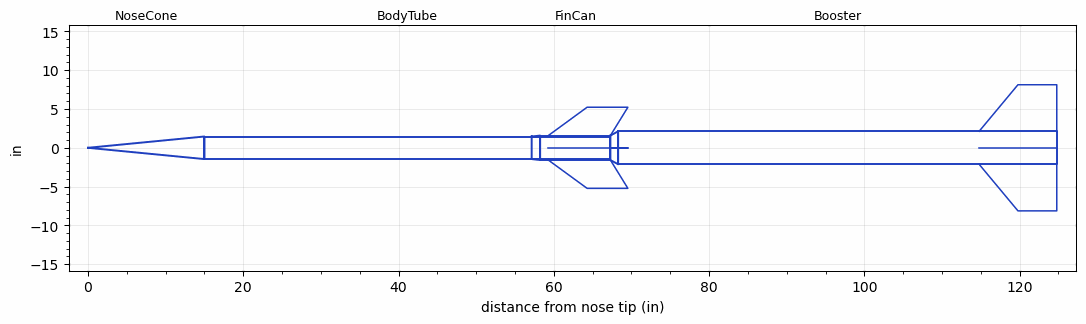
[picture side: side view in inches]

<RASAeroDocument>
 <FileVersion>2</FileVersion>
 <RocketDesign>
  <NoseCone>
   <Length>15</Length>
   <Diameter>2.91</Diameter>
   <Shape>Conical</Shape>
   <BluntRadius>0.1</BluntRadius>
   <Location>0</Location>
  </NoseCone>
  <BodyTube>
   <Length>52.29</Length>
   <Diameter>2.91</Diameter>
   <Location>15</Location>
  </BodyTube>
  <FinCan>
   <Length>9.05</Length>
   <Diameter>3.15</Diameter>
   <InsideDiameter>2.91</InsideDiameter>
   <Location>67.29</Location>
   <ShoulderLength>1.09</ShoulderLength>
   <Offset>-9.05</Offset>
   <Fin>
    <Count>4</Count>
    <Chord>8</Chord>
    <Span>3.65</Span>
    <SweepDistance>5</SweepDistance>
    <TipChord>5.25</TipChord>
    <Thickness>0.157</Thickness>
    <Location>8</Location>
    <AirfoilSection>Hexagonal</AirfoilSection>
    <FX1>1.015</FX1>
    <FX3>0.75</FX3>
   </Fin>
  </FinCan>
  <Booster>
   <Length>56.5</Length>
   <Diameter>4.25</Diameter>
   <InsideDiameter>3.15</InsideDiameter>
   <Location>67.29</Location>
   <ShoulderLength>1</ShoulderLength>
   <Fin>
    <Count>4</Count>
    <Chord>10</Chord>
    <Span>6</Span>
    <SweepDistance>5</SweepDistance>
    <TipChord>5</TipChord>
    <Thickness>0.187</Thickness>
    <Location>10</Location>
    <AirfoilSection>Hexagonal</AirfoilSection>
    <FX1>1</FX1>
    <FX3>0.75</FX3>
   </Fin>
  </Booster>
  <Surface>Rough Camouflage Paint</Surface>
  <ModifiedBarrowman>True</ModifiedBarrowman>
  <Turbulence>True</Turbulence>
  <UseBooster1>True</UseBooster1>
  <UseBooster2>False</UseBooster2>
 </RocketDesign>
 <LaunchSite>
  <Altitude>3701</Altitude>
  <Pressure>29.92</Pressure>
  <RodAngle>0</RodAngle>
  <RodLength>15</RodLength>
  <Temperature>45.8</Temperature>
  <WindSpeed>0</WindSpeed>
 </LaunchSite>
 <Recovery>
  <Altitude1>2000</Altitude1>
  <Altitude2>2000</Altitude2>
  <DeviceType1>Parachute</DeviceType1>
  <DeviceType2>Parachute</DeviceType2>
  <Event1>True</Event1>
  <Event2>True</Event2>
  <Size1>8</Size1>
  <Size2>28</Size2>
  <EventType1>Apogee</EventType1>
  <EventType2>Altitude</EventType2>
  <CD1>0.8</CD1>
  <CD2>1.8</CD2>
 </Recovery>
 <SimulationList>
  <Simulation>
   <SustainerEngine>N3364  (X)</SustainerEngine>
   <SustainerLaunchWt>20.03</SustainerLaunchWt>
   <SustainerNozzleDiameter>2.5</SustainerNozzleDiameter>
   <SustainerCG>41.43</SustainerCG>
   <SustainerIgnitionDelay>15</SustainerIgnitionDelay>
   <Booster1Engine>O8220  (X)</Booster1Engine>
   <Booster1LaunchWt>71.34</Booster1LaunchWt>
   <Booster1SeparationDelay>0</Booster1SeparationDelay>
   <Booster1IgnitionDelay>0</Booster1IgnitionDelay>
   <Booster1CG>80.45</Booster1CG>
   <Booster1NozzleDiameter>3.5</Booster1NozzleDiameter>
   <IncludeBooster1>True</IncludeBooster1>
   <Booster2Delay>0</Booster2Delay>
   <IncludeBooster2>False</IncludeBooster2>
   <TimetoApogee>188.4676</TimetoApogee>
   <MaxAltitude>477283.1</MaxAltitude>
   <MaxVelocity>6171.125</MaxVelocity>
  </Simulation>
 </SimulationList>
</RASAeroDocument>
